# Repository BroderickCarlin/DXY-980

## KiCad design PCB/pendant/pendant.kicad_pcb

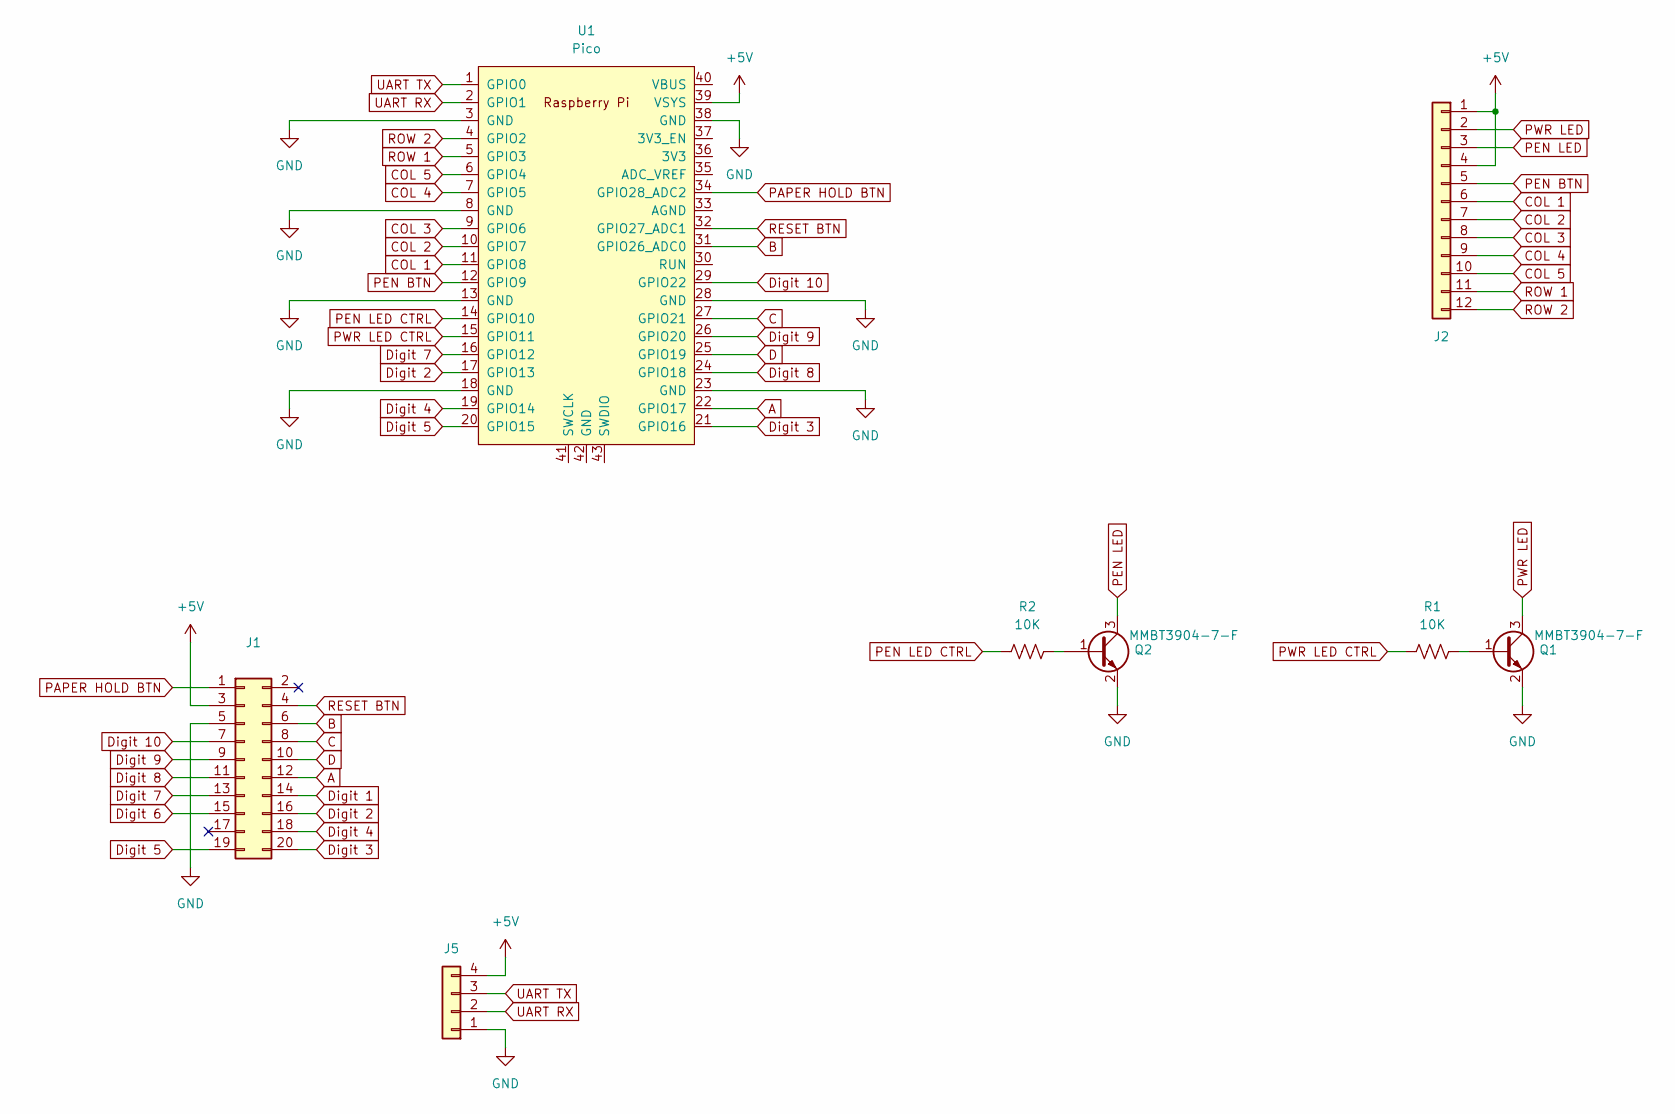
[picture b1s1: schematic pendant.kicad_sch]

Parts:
J1: Conn_02x10_Odd_Even; PinHeader_1x20_P1.27mm_Vertical
J2: Conn_01x12; PinHeader_1x12_P2.54mm_Vertical
J5: Conn_01x04; PinHeader_1x04_P2.54mm_Vertical
Q1, Q2: MMBT3904-7-F; SOT-23
R1, R2: 10K; R_0603_1608Metric
U1: Pico; RPi_Pico_SMD_TH

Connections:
+5V: J1.3, J2.1, J2.4, J5.4, U1.39 (VSYS)
A: J1.12, U1.22 (GPIO17)
B: J1.6, U1.31 (GPIO26_ADC0)
C: J1.8, U1.27 (GPIO21)
COL 1: J2.6, U1.11 (GPIO8)
COL 2: J2.7, U1.10 (GPIO7)
COL 3: J2.8, U1.9 (GPIO6)
COL 4: J2.9, U1.7 (GPIO5)
COL 5: J2.10, U1.6 (GPIO4)
D: J1.10, U1.25 (GPIO19)
Digit 1: J1.14
Digit 2: J1.16, U1.17 (GPIO13)
Digit 3: J1.20, U1.21 (GPIO16)
Digit 4: J1.18, U1.19 (GPIO14)
Digit 5: J1.19, U1.20 (GPIO15)
Digit 6: J1.15
Digit 7: J1.13, U1.16 (GPIO12)
Digit 8: J1.11, U1.24 (GPIO18)
Digit 9: J1.9, U1.26 (GPIO20)
Digit 10: J1.7, U1.29 (GPIO22)
GND: J1.5, J5.1, Q1.2 (E), Q2.2 (E), U1.3 (GND), U1.8 (GND), U1.13 (GND), U1.18 (GND), U1.23 (GND), U1.28 (GND), U1.38 (GND)
unnamed: Q1.1 (B), R1.2
unnamed: Q2.1 (B), R2.2
PAPER HOLD BTN: J1.1, U1.34 (GPIO28_ADC2)
PEN BTN: J2.5, U1.12 (GPIO9)
PEN LED: J2.3, Q2.3 (C)
PEN LED CTRL: R2.1, U1.14 (GPIO10)
PWR LED: J2.2, Q1.3 (C)
PWR LED CTRL: R1.1, U1.15 (GPIO11)
RESET BTN: J1.4, U1.32 (GPIO27_ADC1)
ROW 1: J2.11, U1.5 (GPIO3)
ROW 2: J2.12, U1.4 (GPIO2)
UART RX: J5.2, U1.2 (GPIO1)
UART TX: J5.3, U1.1 (GPIO0)

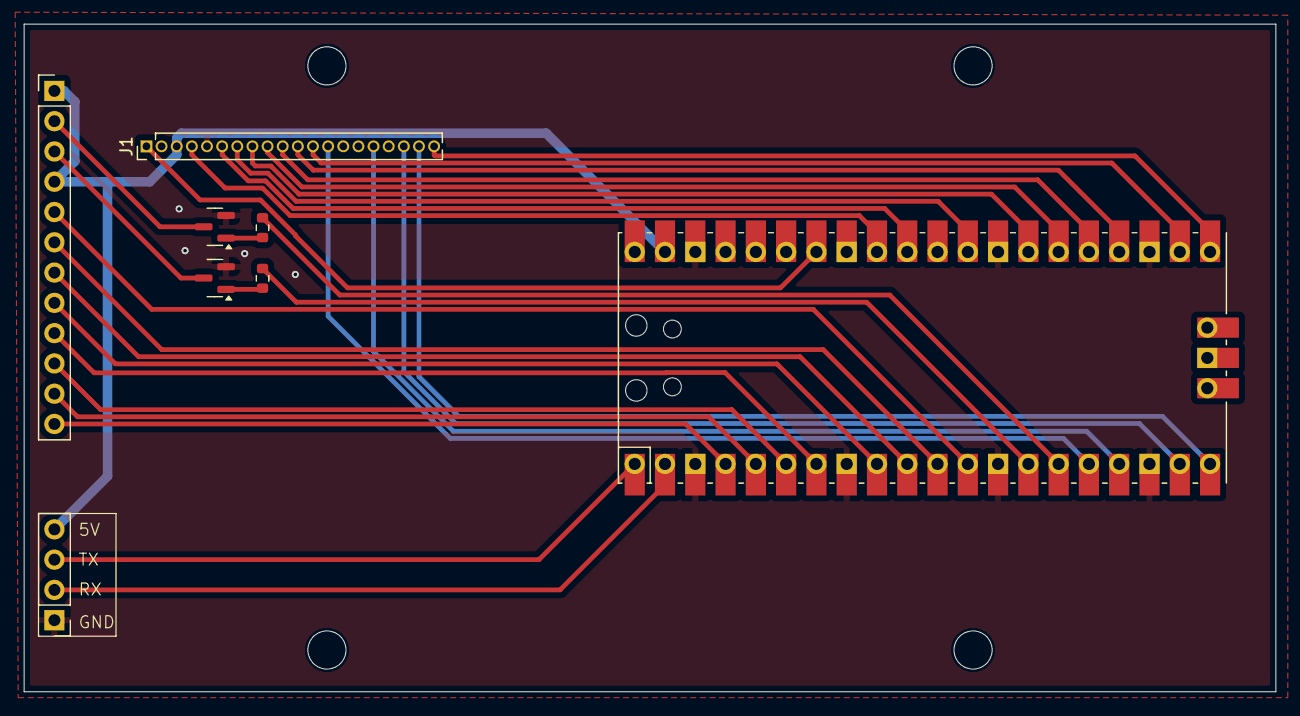
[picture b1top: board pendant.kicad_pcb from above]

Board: 2 copper layers, 105.0 x 56.0 mm, 8 parts (0 on the bottom side), 32 nets.

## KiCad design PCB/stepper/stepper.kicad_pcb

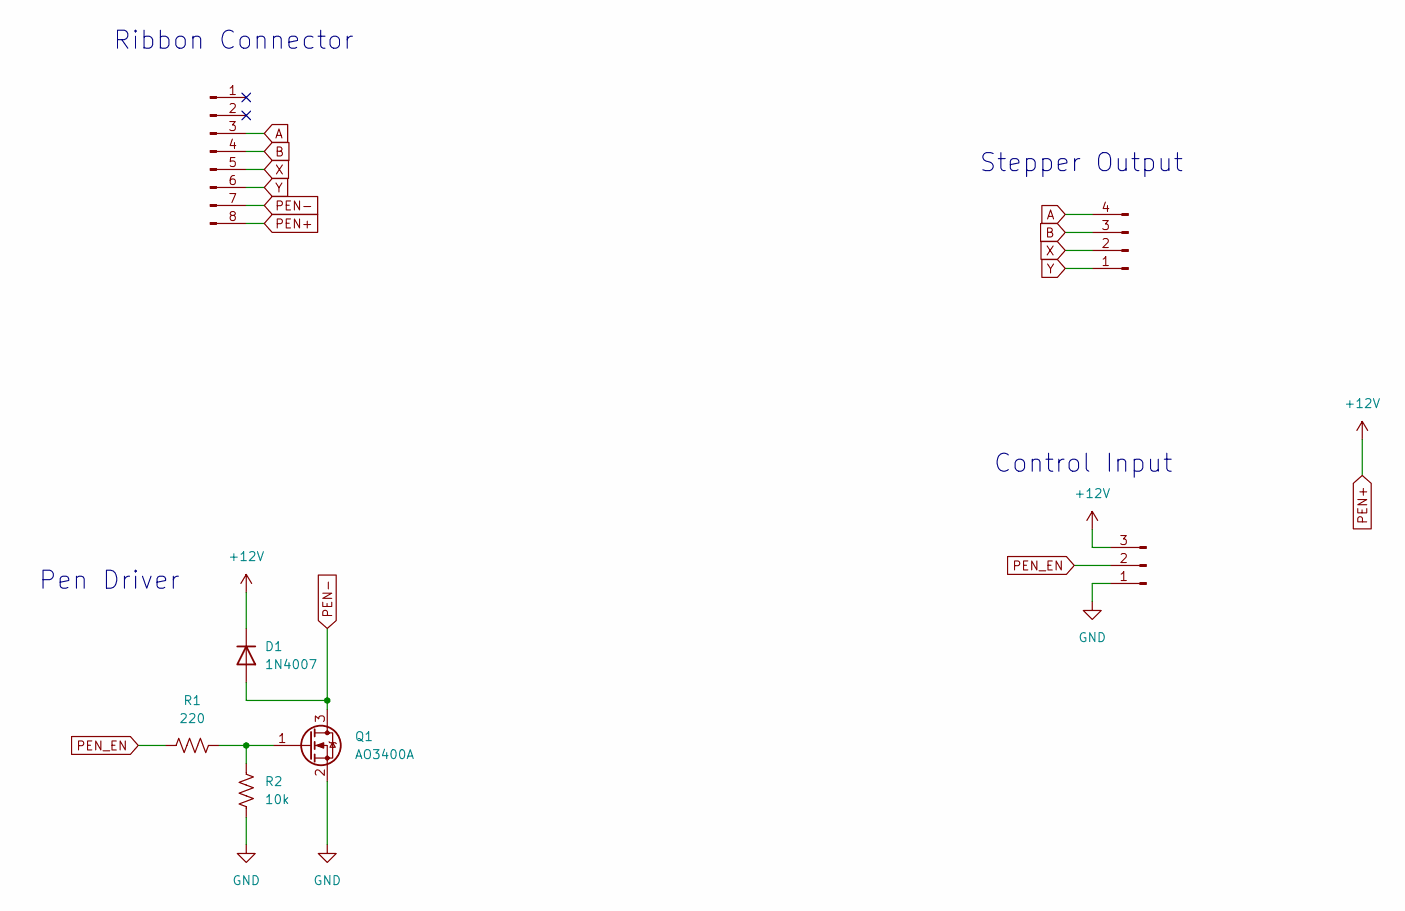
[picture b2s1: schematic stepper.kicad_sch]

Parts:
D1: 1N4007; D_DO-41_SOD81_P10.16mm_Horizontal
J1: Conn_01x08_Pin; TE_Micro-MaTch_215079-8_2x04_P1.27mm_Vertical
J2: Conn_01x04_Pin; TerminalBlock_Phoenix_PT-1,5-4-3.5-H_1x04_P3.50mm_Horizontal
J3: Conn_01x03_Pin; TerminalBlock_Phoenix_PT-1,5-3-3.5-H_1x03_P3.50mm_Horizontal
Q1: AO3400A; SOT-23
R1: 220; R_0603_1608Metric
R2: 10k; R_0603_1608Metric

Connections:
A: J1.3, J2.4
B: J1.4, J2.3
GND: J3.1, Q1.2 (S), R2.2
unnamed: Q1.1 (G), R1.2, R2.1
PEN+: D1.1 (K), J1.8, J3.3
PEN-: D1.2 (A), J1.7, Q1.3 (D)
PEN_EN: J3.2, R1.1
X: J1.5, J2.2
Y: J1.6, J2.1

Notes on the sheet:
Ribbon Connector
Stepper Output
Pen Driver
Control Input

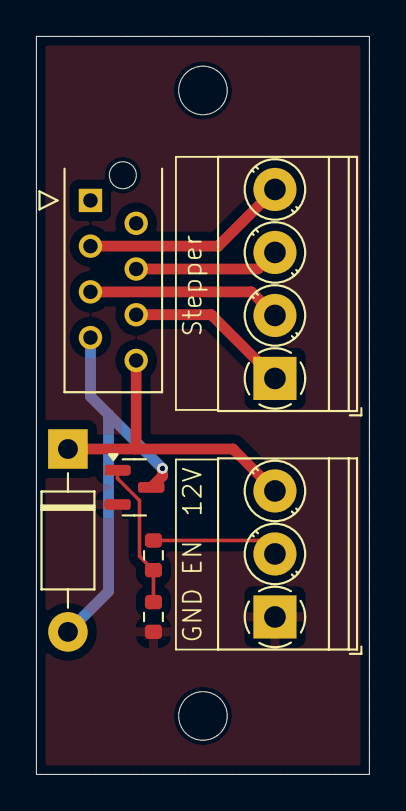
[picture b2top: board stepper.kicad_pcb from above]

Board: 2 copper layers, 18.5 x 41.0 mm, 7 parts (0 on the bottom side), 9 nets.

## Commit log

2024-12-11 chore(Dependabot): bump taskmedia/action-conventional-commits
    Bumps [taskmedia/action-conventional-commits](https://github.com/taskmedia/action-conventional-commits) from 1.1.15 to 1.1.19.
    - [Release notes](https://github.com/taskmedia/action-conventional-commits/releases)
    - [Changelog](https://github.com/taskmedia/action-conventional-commits/blob/main/CHANGELOG.md)
    - [Commits](https://github.com/taskmedia/action-conventional-commits/compare/v1.1.15...v1.1.19)
    ---
    updated-dependencies:
2024-12-16 feat: Restructure and add initial PCB
2025-01-24 feat: Redesign Pendant circuit and add stepper control circuit
2025-01-27 chore(Dependabot): bump taskmedia/action-conventional-commits
    Bumps [taskmedia/action-conventional-commits](https://github.com/taskmedia/action-conventional-commits) from 1.1.19 to 1.1.20.
    - [Release notes](https://github.com/taskmedia/action-conventional-commits/releases)
    - [Changelog](https://github.com/taskmedia/action-conventional-commits/blob/main/CHANGELOG.md)
    - [Commits](https://github.com/taskmedia/action-conventional-commits/compare/v1.1.19...v1.1.20)
    ---
    updated-dependencies:
